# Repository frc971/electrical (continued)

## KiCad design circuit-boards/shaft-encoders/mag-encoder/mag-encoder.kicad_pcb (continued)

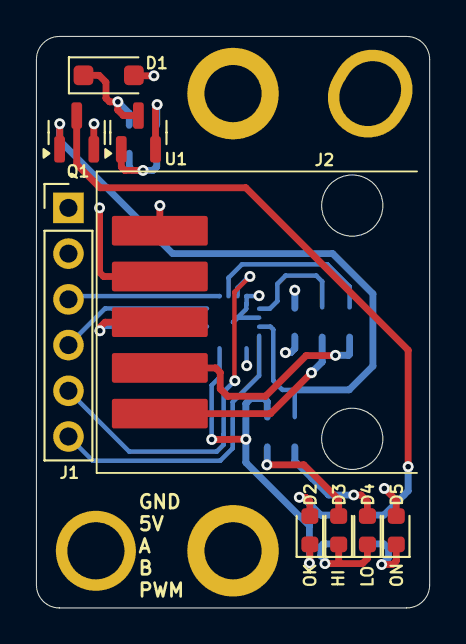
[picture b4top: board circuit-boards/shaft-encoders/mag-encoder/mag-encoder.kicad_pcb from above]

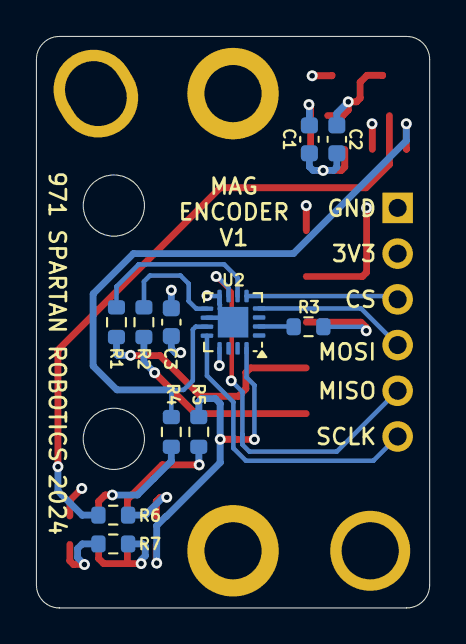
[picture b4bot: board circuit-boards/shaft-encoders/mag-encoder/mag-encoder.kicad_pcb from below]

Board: 4 copper layers, 21.8 x 31.8 mm, 24 parts (11 on the bottom side), 21 nets.

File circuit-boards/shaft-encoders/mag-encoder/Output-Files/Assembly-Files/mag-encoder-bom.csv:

"Item","QUANTITY","Reference","Value","MFG","MFG P/N","DIST","DIST P/N"
"1","3","C1-C3","1uF-10%-25V-0603","Kyocera","06033C105KAT2A","Digikey","478-10046-1-ND"
"2","1","D1","NRVB120VLSFT1G","onsemi","NRVB120VLSFT1G","Digikey","NRVB120VLSFT1GOSCT-ND"
"3","2","D2,D5","-- mixed values --","Wurth Electronik","150060GS75000","Digikey","732-4971-1-ND"
"4","2","D3,D4","-- mixed values --","Wurth Electronik","150060RS75000","Digikey","732-4978-1-ND"
"5","1","J2","0015912055","Molex","0015912055","Digikey","WM1343-ND"
"6","1","Q1","BSS84","onsemi","BSS84","Digikey","BSS84CT-ND"
"7","3","R1-R3","100R-1%-0603","YAGEO","RC0603FR-07100RL","Digikey","311-100HRCT-ND"
"8","4","R4-R7","1.00k-1%-0603","YAGEO","RC0603FR-071KL","Digikey","311-1.00KHRCT-ND"
"9","1","U1","AP2120N-3.3TRG1","Diodes Inc","AP2120N-3.3TRG1","Digikey","AP2120N-3.3TRG1DICT-ND"
"10","1","U2","MA732GQ","Monolithic Power Systems","MA732GQ-Z","Digikey","1589-MA732GQ-ZCT-ND"

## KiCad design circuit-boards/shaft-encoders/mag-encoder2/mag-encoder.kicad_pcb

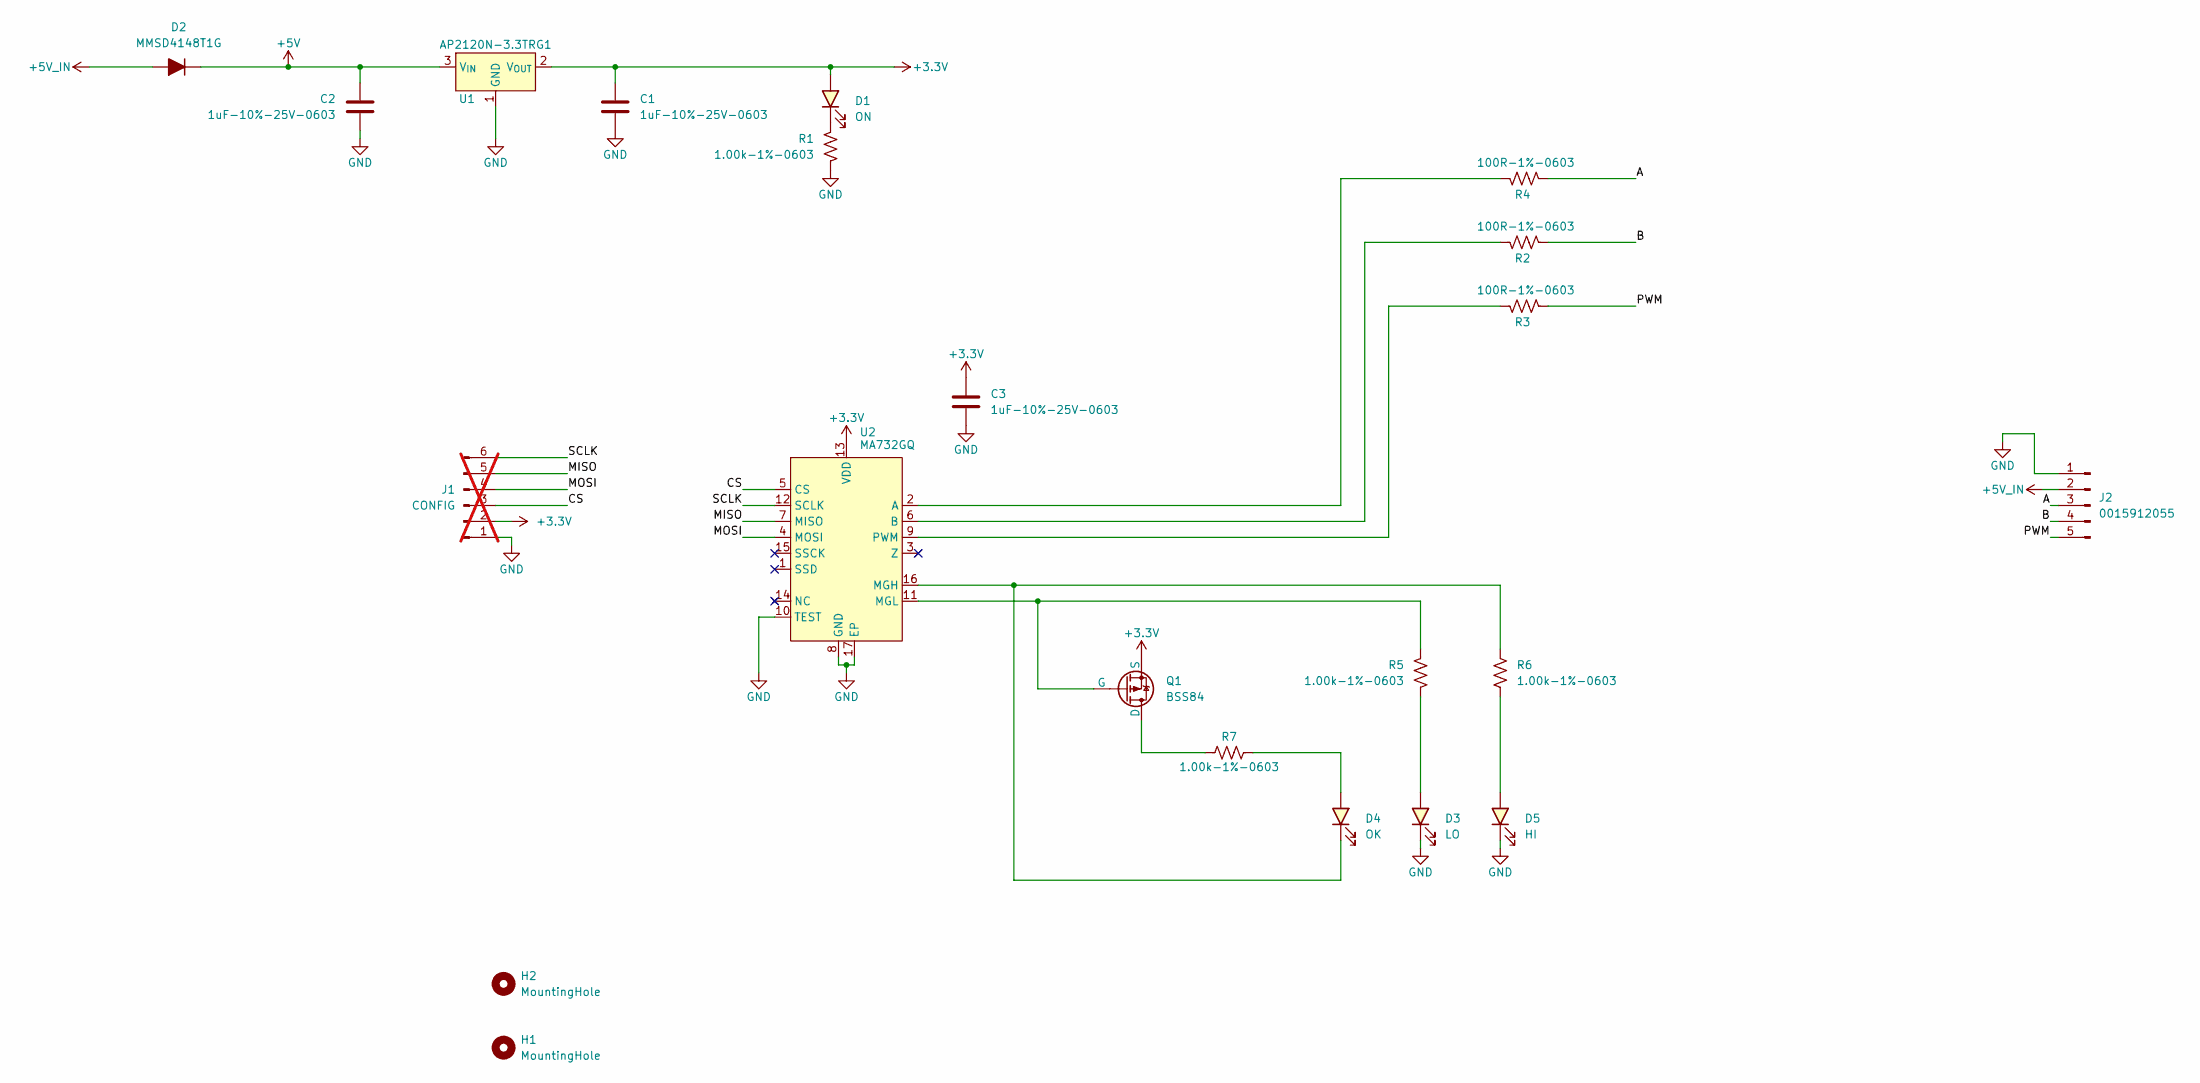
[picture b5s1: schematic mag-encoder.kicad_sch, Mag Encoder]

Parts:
C1, C2, C3: 1uF-10%-25V-0603; C_0603_1608Metric; MFG P/N 06033C105KAT2A
D1: ON; LED_0603_1608Metric; MFG P/N 150060YS75000
D2: MMSD4148T1G; D_SOD-123; MFG P/N MMSD4148T1G
D3: LO; LED_0603_1608Metric; MFG P/N 150060RS75000
D4: OK; LED_0603_1608Metric; MFG P/N 150060VS75000
D5: HI; LED_0603_1608Metric; MFG P/N 150060RS75000
H1, H2: MountingHole; pin-0.100
J1: CONFIG; PinHeader_1x06_P2.54mm_Vertical; not fitted
J2: 0015912055; Molex-70634-0039; MFG P/N 0015912055
Q1: BSS84; SOT-23; MFG P/N BSS84
R1, R5, R6, R7: 1.00k-1%-0603; R_0603_1608Metric; MFG P/N RC0603FR-071KL
R2, R3, R4: 100R-1%-0603; R_0603_1608Metric; MFG P/N RC0603FR-07100RL
U1: AP2120N-3.3TRG1; SOT-23; MFG P/N AP2120N-3.3TRG1
U2: MA732GQ; QFN-16-1EP_3x3mm_P0.5mm_EP1.7x1.7mm; MFG P/N MA732GQ-Z

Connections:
+3.3V: C1.1, C3.1, D1.2 (A), J1.2, Q1.2 (S), U1.2 (V_{OUT}), U2.13 (VDD)
+5V: C2.1, D2.1 (K), U1.3 (V_{IN})
+5V_IN: D2.2 (A), J2.2
/A: J2.3, R4.2
/B: J2.4, R2.2
/CS: J1.3, U2.5 (CS)
/MISO: J1.5, U2.7 (MISO)
/MOSI: J1.4, U2.4 (MOSI)
/PWM: J2.5, R3.2
/SCLK: J1.6, U2.12 (SCLK)
GND: C1.2, C2.2, C3.2, D3.1 (K), D5.1 (K), J1.1, J2.1, R1.2, U1.1 (GND), U2.8 (GND), U2.10 (TEST), U2.17 (EP)
unnamed: D1.1 (K), R1.1
unnamed: D3.2 (A), R5.2
unnamed: D4.2 (A), R7.2
unnamed: D4.1 (K), R6.1, U2.16 (MGH)
unnamed: D5.2 (A), R6.2
unnamed: Q1.3 (D), R7.1
unnamed: Q1.1 (G), R5.1, U2.11 (MGL)
unnamed: R4.1, U2.2 (A)
unnamed: R2.1, U2.6 (B)
unnamed: R3.1, U2.9 (PWM)

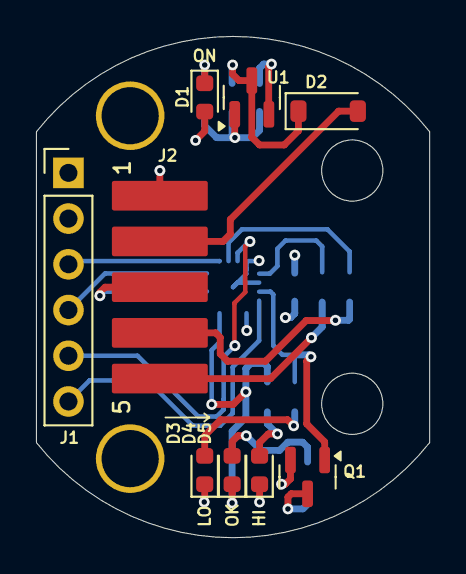
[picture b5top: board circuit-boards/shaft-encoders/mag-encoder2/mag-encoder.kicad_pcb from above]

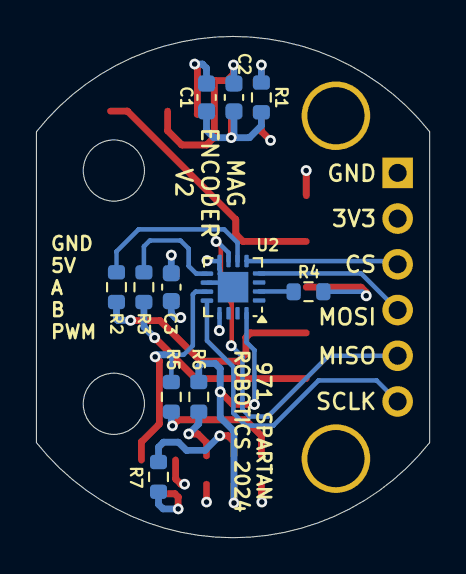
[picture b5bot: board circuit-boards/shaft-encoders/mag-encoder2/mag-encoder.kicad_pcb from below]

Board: 4 copper layers, 21.8 x 27.8 mm, 22 parts (11 on the bottom side), 21 nets.

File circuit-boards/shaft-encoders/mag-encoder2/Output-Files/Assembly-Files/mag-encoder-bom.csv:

"Item","QUANTITY","Reference","Value","MFG","MFG P/N","DIST","DIST P/N"
"1","3","C1-C3","1uF-10%-25V-0603","Kyocera","06033C105KAT2A","Digikey","478-10046-1-ND"
"2","1","D1","ON","Wurth Electronik","150060YS75000","Digikey","732-4981-1-ND"
"3","1","D2","MMSD4148T1G","onsemi","MMSD4148T1G","Digikey","MMSD4148T1GOSCT-ND"
"4","1","D4","OK","Wurth Electronik","150060VS75000","Digikey","732-4980-1-ND"
"5","2","D3,D5","-- mixed values --","Wurth Electronik","150060RS75000","Digikey","732-4978-1-ND"
"6","1","J2","0015912055","Molex","0015912055","Digikey","WM1343-ND"
"7","1","Q1","BSS84","onsemi","BSS84","Digikey","BSS84CT-ND"
"8","4","R1,R5-R7","1.00k-1%-0603","YAGEO","RC0603FR-071KL","Digikey","311-1.00KHRCT-ND"
"9","3","R2-R4","100R-1%-0603","YAGEO","RC0603FR-07100RL","Digikey","311-100HRCT-ND"
"10","1","U1","AP2120N-3.3TRG1","Diodes Inc","AP2120N-3.3TRG1","Digikey","AP2120N-3.3TRG1DICT-ND"
"11","1","U2","MA732GQ","Monolithic Power Systems","MA732GQ-Z","Digikey","1589-MA732GQ-ZCT-ND"

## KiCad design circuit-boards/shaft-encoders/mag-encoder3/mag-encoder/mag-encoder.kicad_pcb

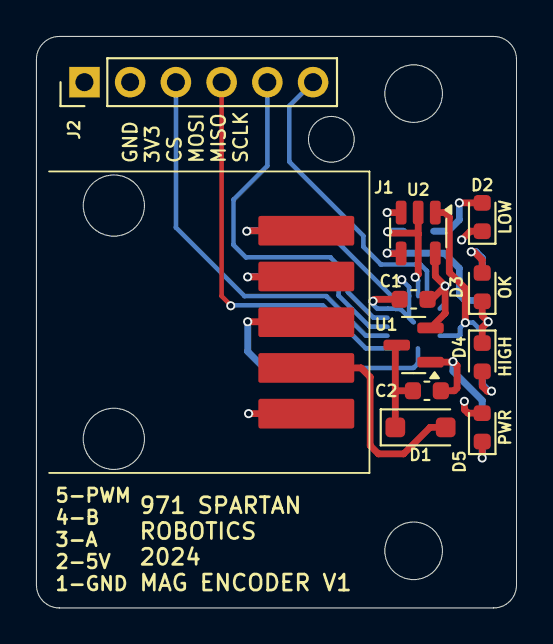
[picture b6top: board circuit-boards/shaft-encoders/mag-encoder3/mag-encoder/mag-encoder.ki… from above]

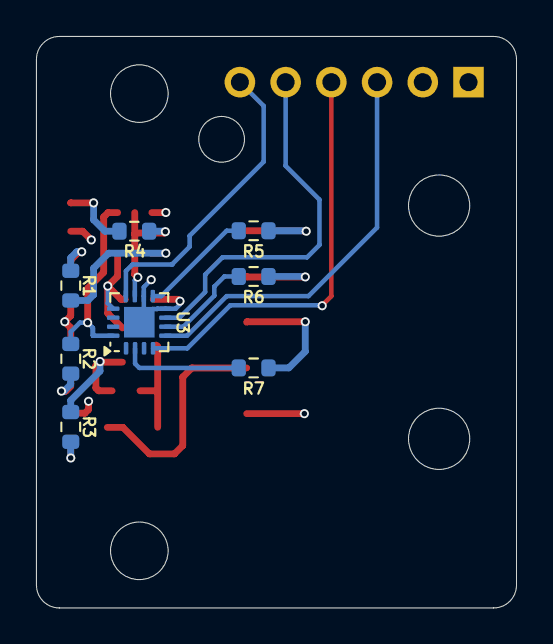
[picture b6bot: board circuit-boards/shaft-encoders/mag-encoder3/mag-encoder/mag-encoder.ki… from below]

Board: 4 copper layers, 26.7 x 31.8 mm, 23 parts (8 on the bottom side), 21 nets.

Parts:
C1, C2: 1uF-10%-25V-0603; C_0603_1608Metric
D1: NRVB120VLSFT1G; D_SOD-123F
D2: LOW; LED_0603_1608Metric
D3: OK; LED_0603_1608Metric
D4: HIGH; LED_0603_1608Metric
D5: PWR; LED_0603_1608Metric
H1, H2: MountingHole; MountingHole_3.2mm_M3
H3: Pin; pin-0.100
H4: Slot; slot-0.100x0.120
J1: 0015912055; Molex-70634-0039
J2: CONFIG; PinHeader_1x06_P2.54mm_Vertical
R1, R2, R3, R4: 1.00k-1%-0603; R_0603_1608Metric
R5, R6, R7: 100R-1%-0603; R_0603_1608Metric
U1: AP2120N-3.3TRG1; SOT-23
U2: SN74LVC1G02DBVR; SOT-23-5
U3: MA732GQ; QFN-16-1EP_3x3mm_P0.5mm_EP1.7x1.7mm

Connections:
+3.3V: C1.1, D5.2 (A), J2.2, U1.2 (V_{OUT}), U2.5 (VCC), U3.13 (VDD)
+5V: C2.1, D1.1 (K), U1.3 (V_{IN})
+5V_IN: D1.2 (A), J1.2
/A: J1.3, R7.2
/B: J1.4, R6.2
/CS: J2.3, U3.5 (CS)
/MISO: J2.5, U3.7 (MISO)
/MOSI: J2.4, U3.4 (MOSI)
/PWM: J1.5, R5.2
/SCLK: J2.6, U3.12 (SCLK)
GND: C1.2, C2.2, D2.1 (K), D3.1 (K), D4.1 (K), J1.1, J2.1, R3.2, U1.1 (GND), U2.3 (GND), U3.8 (GND), U3.10 (TEST), U3.17 (EP)
unnamed: D2.2 (A), R4.2
unnamed: D3.2 (A), R1.2
unnamed: D4.2 (A), R2.2
unnamed: D5.1 (K), R3.1
unnamed: R1.1, U2.4
unnamed: R7.1, U3.2 (A)
unnamed: R6.1, U3.6 (B)
unnamed: R2.1, U2.1, U3.16 (MGH)
unnamed: R4.1, U2.2, U3.11 (MGL)
unnamed: R5.1, U3.9 (PWM)

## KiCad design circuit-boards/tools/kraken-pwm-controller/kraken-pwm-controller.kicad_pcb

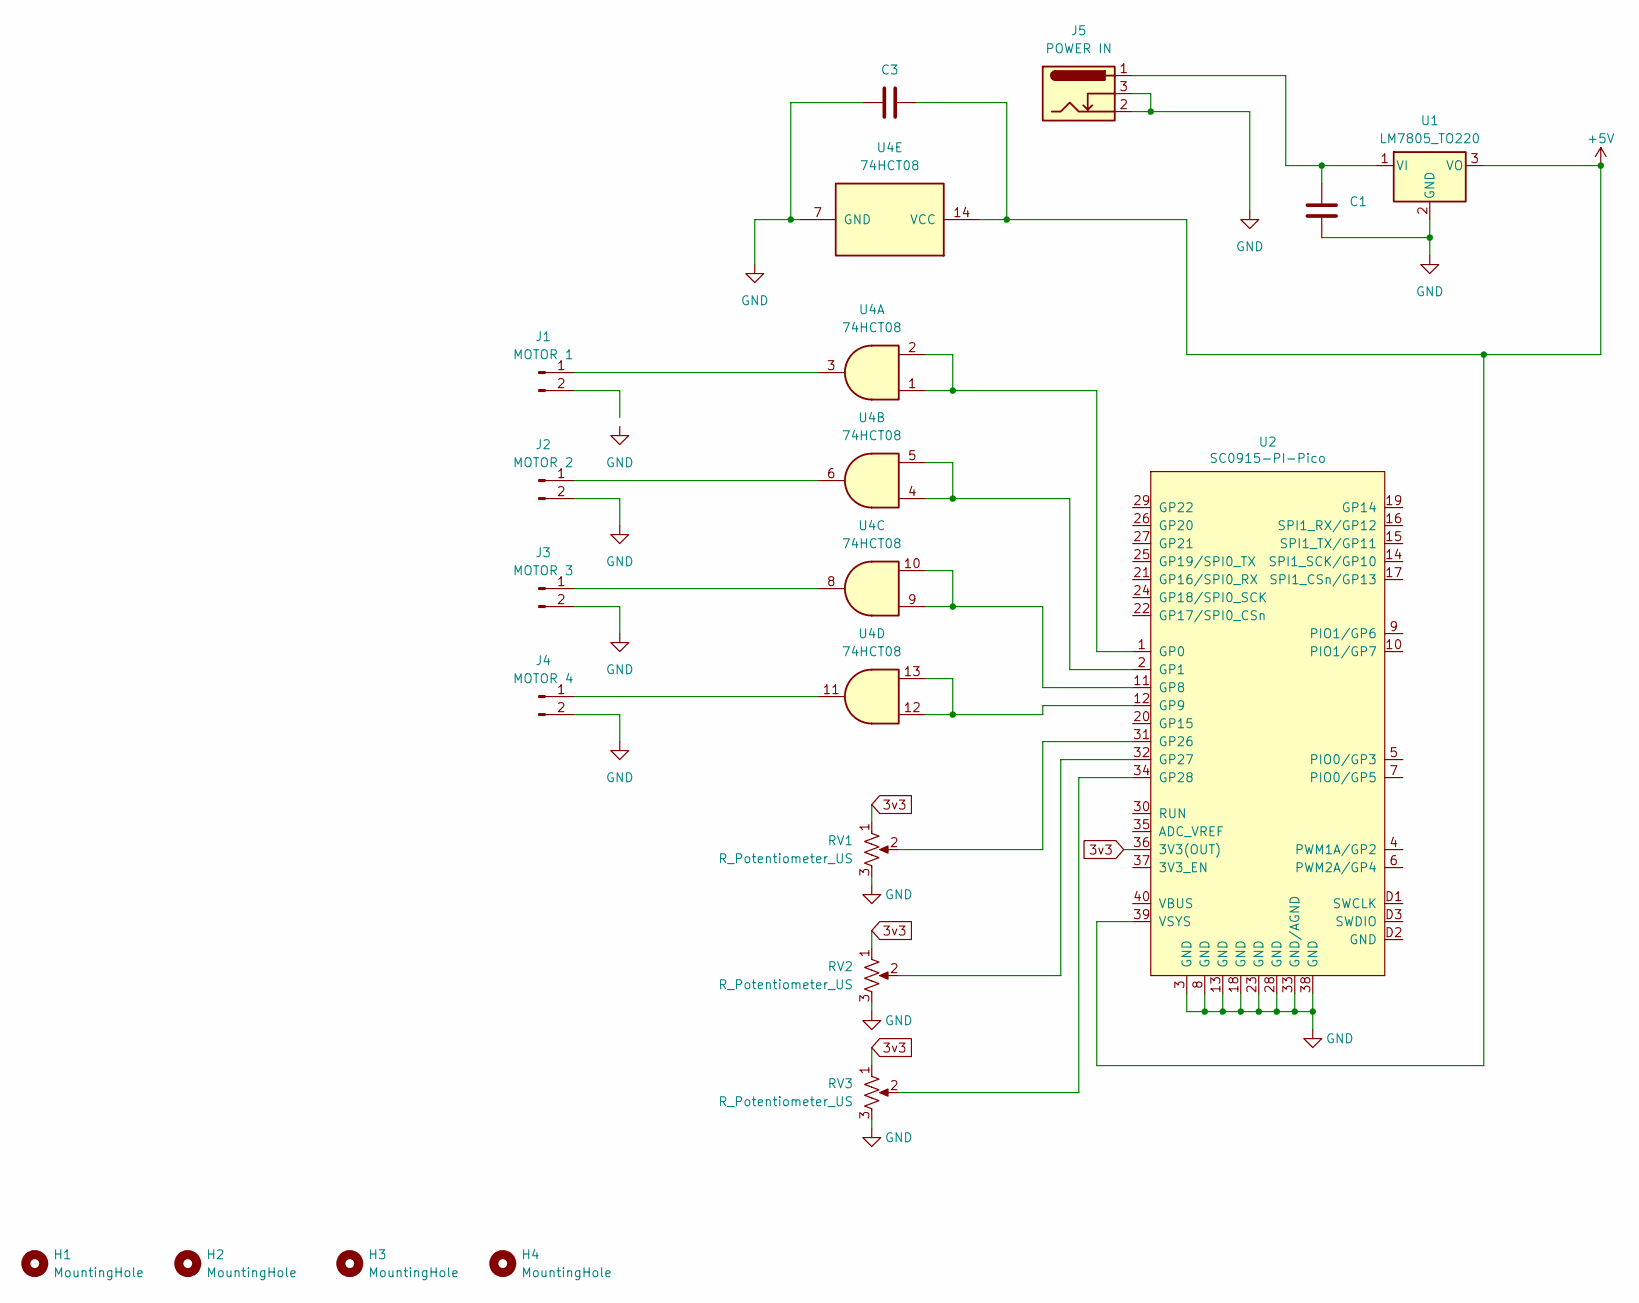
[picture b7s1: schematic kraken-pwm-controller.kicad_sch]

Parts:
C1, C3: CAP_R82D-7P4X3P6-5P0_KEM
H1, H2, H3, H4: MountingHole; MountingHole_3.2mm_M3
J1: MOTOR 1; 2 PIN RIGHT ANGLE MOLEX SL
J2: MOTOR 2; 2 PIN RIGHT ANGLE MOLEX SL
J3: MOTOR 3; 2 PIN RIGHT ANGLE MOLEX SL
J4: MOTOR 4; 2 PIN RIGHT ANGLE MOLEX SL
J5: POWER IN; BARREL JACK CONNECTOR
RV1, RV2, RV3: R_Potentiometer_US; PTV09A4020FB103
U1: LM7805_TO220; TO-220-3_Vertical
U2: SC0915-PI-Pico; PICO
U4: 74HCT08; N14

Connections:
3v3: RV1.1, RV2.1, RV3.1, U2.36 (3V3(OUT))
+5V: C3.1, U1.3 (VO), U2.39 (VSYS), U4.14 (VCC)
GND: C1.1, C3.2, J2.2, J3.2, J4.2, J5.2, J5.3, RV1.3, RV2.3, RV3.3, U1.2 (GND), U2.3 (GND), U2.8 (GND), U2.13 (GND), U2.18 (GND), U2.23 (GND), U2.28 (GND), U2.33 (GND/AGND), U2.38 (GND), U4.7 (GND)
unnamed: J1.1, U4.3
unnamed: J2.1, U4.6
unnamed: J3.1, U4.8
unnamed: J4.1, U4.11
unnamed: C1.2, J5.1, U1.1 (VI)
unnamed: U2.1 (GP0), U4.1, U4.2
unnamed: U2.2 (GP1), U4.4, U4.5
unnamed: U2.11 (GP8), U4.9, U4.10
unnamed: U2.12 (GP9), U4.12, U4.13
unnamed: RV1.2, U2.31 (GP26)
unnamed: RV2.2, U2.32 (GP27)
unnamed: RV3.2, U2.34 (GP28)

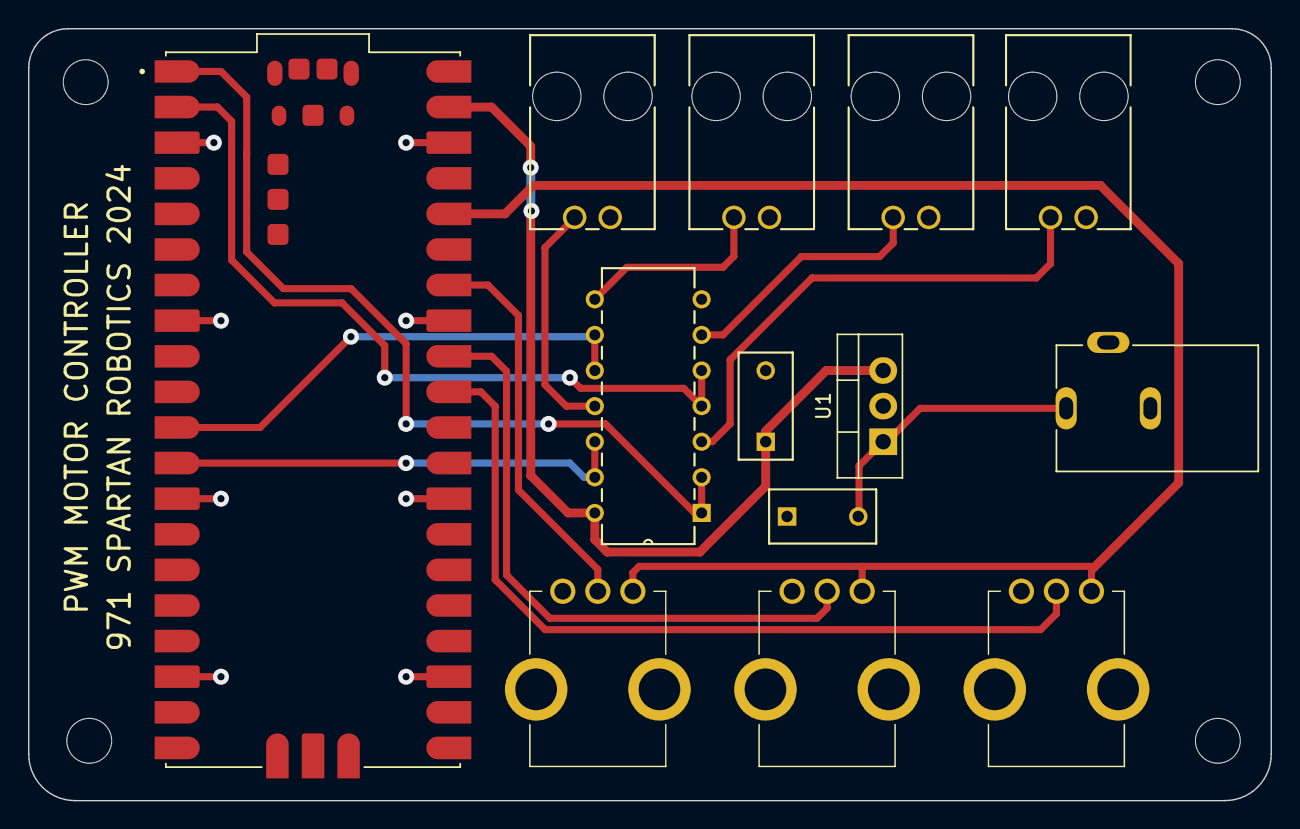
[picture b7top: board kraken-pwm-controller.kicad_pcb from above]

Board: 2 copper layers, 88.6 x 55.1 mm, 17 parts (0 on the bottom side), 15 nets.
